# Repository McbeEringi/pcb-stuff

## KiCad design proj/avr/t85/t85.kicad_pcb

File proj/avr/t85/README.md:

# ATtiny85 Micronucleus 開発ボード

## 機能

- 超小型8ピンDIPサイズ
- LEDとボタンを搭載
- EDLC電源基板付き

## 部品

- [ATTiny85](https://akizukidenshi.com/catalog/g/gI-09574/)
- バイパスコンデンサ 1608サイズ 大きめに4.7uFとか
- [表面実装タクトスイッチ](https://akizukidenshi.com/catalog/g/gP-14888/)
- LED
  - 1608サイズ LED
  - 1608サイズ LED電流制限抵抗 10kとか
- USB部
  - CC用抵抗 1608サイズ 5.1k *2
  - ダンピング抵抗 1608サイズ 100R(47Rも可) *2
  - プルアップ抵抗 1608サイズ 1.5k
  - [ツェナーダイオード 3.6v SOD323Fパッケージ(UMD2)](https://akizukidenshi.com/catalog/g/gI-07435/) *2

## 組み立て

表にスイッチとチップ部品

```text
 | USB |
   S W
     101
     -Z<-
-|<- 101
103  -Z<-
-||- 152
```

裏にattiny85と5k1*2
シルクが長いところに凹みを合わせる

SW@PB0
LED@PB1

## ブートローダーの書き込み

<https://github.com/micronucleus/micronucleus>をビルド
windowsはドライバをインストール
ファームウェアをISP書き込み機を用いてを書き込む

参考
<https://qiita.com/nak435/items/67aca33ca49b6f328faa>

## 作例

4和音電子オルゴール <https://github.com/McbeEringi/avr-musicbox>

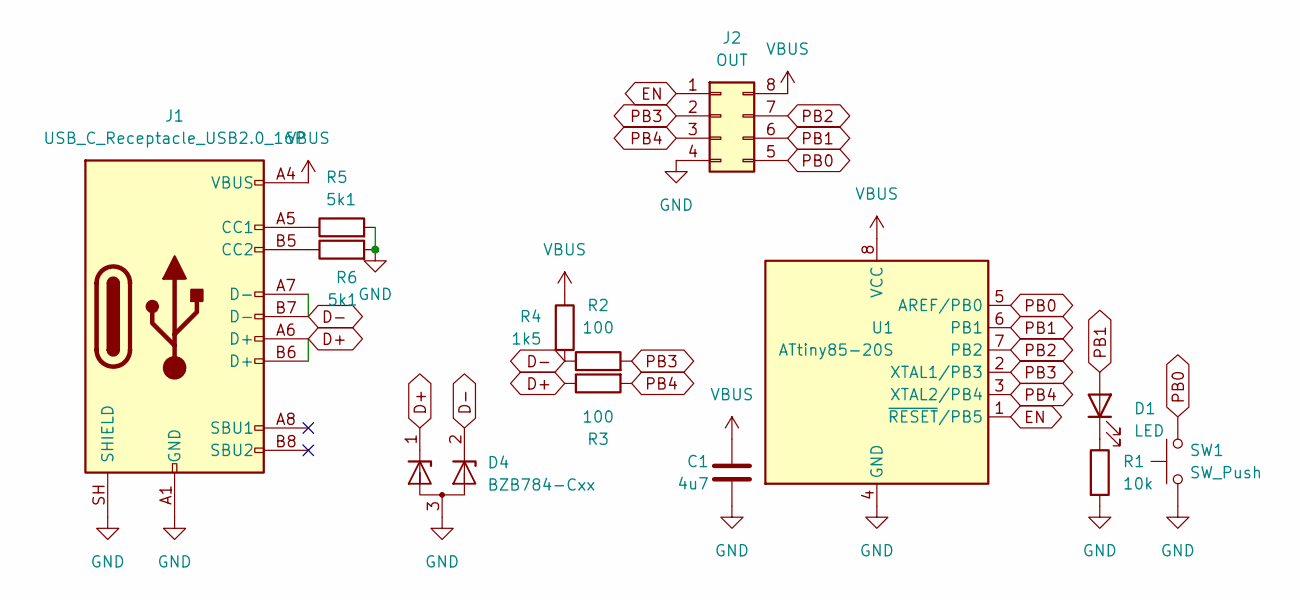
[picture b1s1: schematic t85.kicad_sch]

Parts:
C1: 4u7; C_0603_1608Metric
D1: LED; LED_0603_1608Metric
D4: BZB784-Cxx; SOT-323_SC-70
J1: USB_C_Receptacle_USB2.0_16P; USB_C_Receptacle_GCT_USB4105-xx-A_16P_TopMnt_Horizontal
J2: OUT; DIP-8_W7.62mm_Socket
R1: 10k; R_0603_1608Metric
R2, R3: 100; R_0603_1608Metric
R4: 1k5; R_0603_1608Metric
R5, R6: 5k1; R_0603_1608Metric
SW1: SW_Push; alps-skrp
U1: ATtiny85-20S; SOIC-8_5.3x5.3mm_P1.27mm

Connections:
D+: D4.1 (K), J1.A6 (D+), J1.B6 (D+), R3.1
D-: D4.2 (K), J1.A7 (D-), J1.B7 (D-), R2.1, R4.2
EN: J2.1, U1.1 (~RESET/PB5)
GND: C1.2, D4.3 (A), J1.A1 (GND), J1.A12 (GND), J1.B1 (GND), J1.B12 (GND), J1.SH (SHIELD), J2.4, R1.2, R5.2, R6.2, SW1.1, U1.4 (GND)
unnamed: D1.1 (K), R1.1
unnamed: J1.A5 (CC1), R5.1
unnamed: J1.B5 (CC2), R6.1
PB0: J2.5, SW1.2, U1.5 (AREF/PB0)
PB1: D1.2 (A), J2.6, U1.6 (PB1)
PB2: J2.7, U1.7 (PB2)
PB3: J2.2, R2.2, U1.2 (XTAL1/PB3)
PB4: J2.3, R3.2, U1.3 (XTAL2/PB4)
VBUS: C1.1, J1.A4 (VBUS), J1.A9 (VBUS), J1.B4 (VBUS), J1.B9 (VBUS), J2.8, R4.1, U1.8 (VCC)

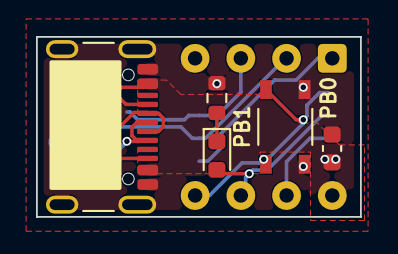
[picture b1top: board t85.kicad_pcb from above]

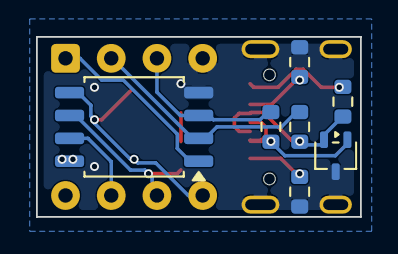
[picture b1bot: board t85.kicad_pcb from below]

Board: 2 copper layers, 18.0 x 10.0 mm, 13 parts (7 on the bottom side), 13 nets.

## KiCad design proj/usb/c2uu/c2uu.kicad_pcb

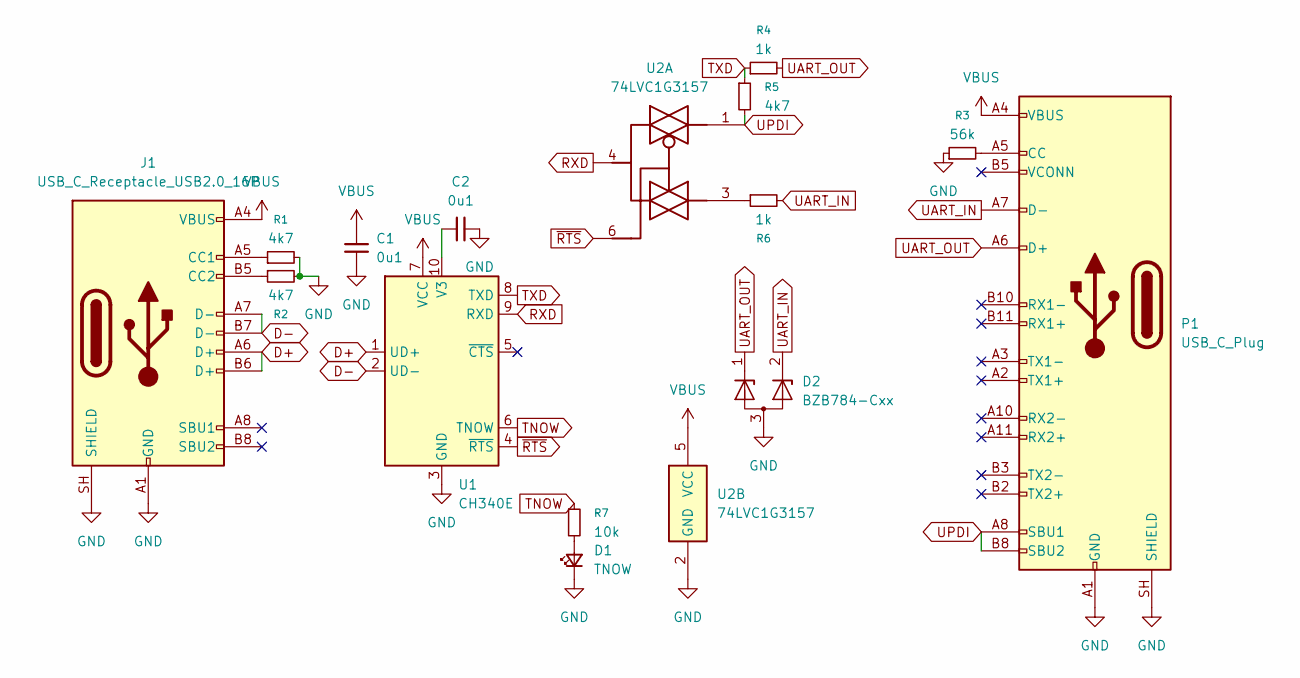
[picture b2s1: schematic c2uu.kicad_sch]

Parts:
C1, C2: 0u1; C_0603_1608Metric
D1: TNOW; LED_0603_1608Metric
D2: BZB784-Cxx; SOT-323_SC-70
J1: USB_C_Receptacle_USB2.0_16P; USB_C_Receptacle_GCT_USB4105-xx-A_16P_TopMnt_Horizontal
P1: USB_C_Plug; USB_C_Plug_24P
R1, R2, R5: 4k7; R_0603_1608Metric
R3: 56k; R_0603_1608Metric
R4, R6: 1k; R_0603_1608Metric
R7: 10k; R_0603_1608Metric
U1: CH340E; MSOP-10_3x3mm_P0.5mm
U2: 74LVC1G3157; SOT-363_SC-70-6

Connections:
D+: J1.A6 (D+), J1.B6 (D+), U1.1 (UD+)
D-: J1.A7 (D-), J1.B7 (D-), U1.2 (UD-)
GND: C1.2, C2.2, D1.1 (K), D2.3 (A), J1.A1 (GND), J1.A12 (GND), J1.B1 (GND), J1.B12 (GND), J1.SH (SHIELD), P1.A1 (GND), P1.A12 (GND), P1.B1 (GND), P1.B12 (GND), P1.SH (SHIELD), R1.2, R2.2, R3.1, U1.3 (GND), U2.2 (GND)
unnamed: D1.2 (A), R7.2
unnamed: J1.A5 (CC1), R1.1
unnamed: J1.B5 (CC2), R2.1
unnamed: P1.A5 (CC), R3.2
unnamed: R6.1, U2.3
unnamed: C2.1, U1.10 (V3)
RXD: U1.9 (RXD), U2.4
TNOW: R7.1, U1.6 (TNOW)
TXD: R4.1, R5.1, U1.8 (TXD)
UART_IN: D2.2 (K), P1.A7 (D-), R6.2
UART_OUT: D2.1 (K), P1.A6 (D+), R4.2
UPDI: P1.A8 (SBU1), P1.B8 (SBU2), R5.2, U2.1
VBUS: C1.1, J1.A4 (VBUS), J1.A9 (VBUS), J1.B4 (VBUS), J1.B9 (VBUS), P1.A4 (VBUS), P1.A9 (VBUS), P1.B4 (VBUS), P1.B9 (VBUS), U1.7 (VCC), U2.5 (VCC)
~RTS: U1.4 (~RTS), U2.6

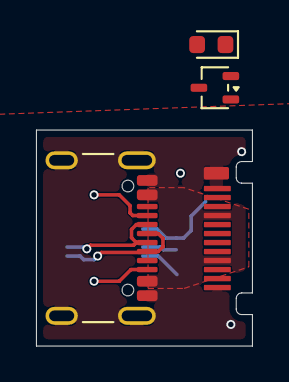
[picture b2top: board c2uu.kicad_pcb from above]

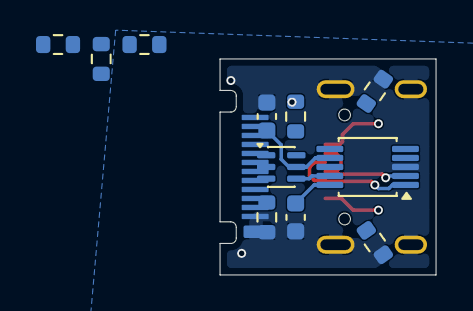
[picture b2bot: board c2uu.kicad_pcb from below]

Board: 2 copper layers, 12.0 x 12.0 mm, 15 parts (12 on the bottom side), 17 nets.

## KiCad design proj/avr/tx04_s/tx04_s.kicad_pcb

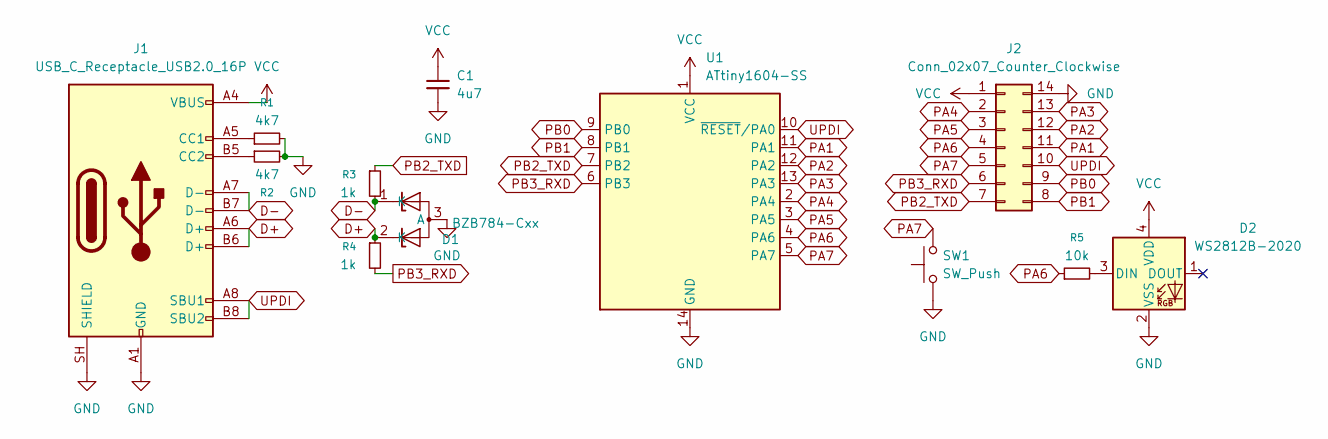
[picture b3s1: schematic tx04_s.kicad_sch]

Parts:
C1: 4u7; C_0603_1608Metric
D1: BZB784-Cxx; SOT-323_SC-70
D2: WS2812B-2020; LED_WS2812B-2020_PLCC4_2.0x2.0mm
J1: USB_C_Receptacle_USB2.0_16P; USB_C_Receptacle_GCT_USB4105-xx-A_16P_TopMnt_Horizontal
J2: Conn_02x07_Counter_Clockwise; DIP-14_W10.16mm
R1, R2: 4k7; R_0603_1608Metric
R3, R4: 1k; R_0603_1608Metric
R5: 10k; R_0603_1608Metric
SW1: SW_Push; alps-skrp
U1: ATtiny1604-SS; SOIC-14_3.9x8.7mm_P1.27mm

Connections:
D+: D1.2 (K), J1.A6 (D+), J1.B6 (D+), R4.1
D-: D1.1 (K), J1.A7 (D-), J1.B7 (D-), R3.2
GND: C1.2, D1.3 (A), D2.2 (VSS), J1.A1 (GND), J1.A12 (GND), J1.B1 (GND), J1.B12 (GND), J1.SH (SHIELD), J2.14, R1.2, R2.2, SW1.1, U1.14 (GND)
unnamed: D2.3 (DIN), R5.2
unnamed: J1.A5 (CC1), R1.1
unnamed: J1.B5 (CC2), R2.1
PA1: J2.11, U1.11 (PA1)
PA2: J2.12, U1.12 (PA2)
PA3: J2.13, U1.13 (PA3)
PA4: J2.2, U1.2 (PA4)
PA5: J2.3, U1.3 (PA5)
PA6: J2.4, R5.1, U1.4 (PA6)
PA7: J2.5, SW1.2, U1.5 (PA7)
PB0: J2.9, U1.9 (PB0)
PB1: J2.8, U1.8 (PB1)
PB2_TXD: J2.7, R3.1, U1.7 (PB2)
PB3_RXD: J2.6, R4.2, U1.6 (PB3)
UPDI: J1.A8 (SBU1), J1.B8 (SBU2), J2.10, U1.10 (~RESET/PA0)
VCC: C1.1, D2.4 (VDD), J1.A4 (VBUS), J1.A9 (VBUS), J1.B4 (VBUS), J1.B9 (VBUS), J2.1, U1.1 (VCC)

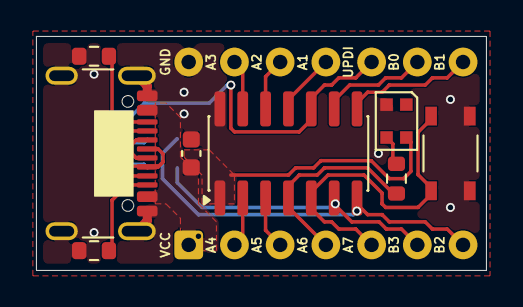
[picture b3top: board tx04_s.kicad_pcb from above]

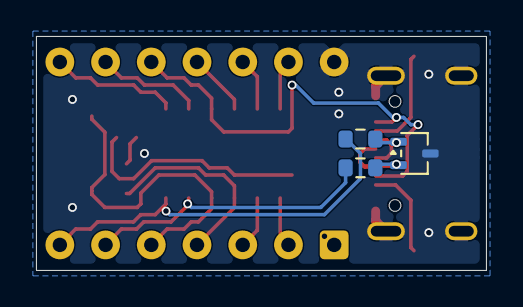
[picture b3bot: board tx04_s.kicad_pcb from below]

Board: 2 copper layers, 25.0 x 13.0 mm, 12 parts (3 on the bottom side), 19 nets.

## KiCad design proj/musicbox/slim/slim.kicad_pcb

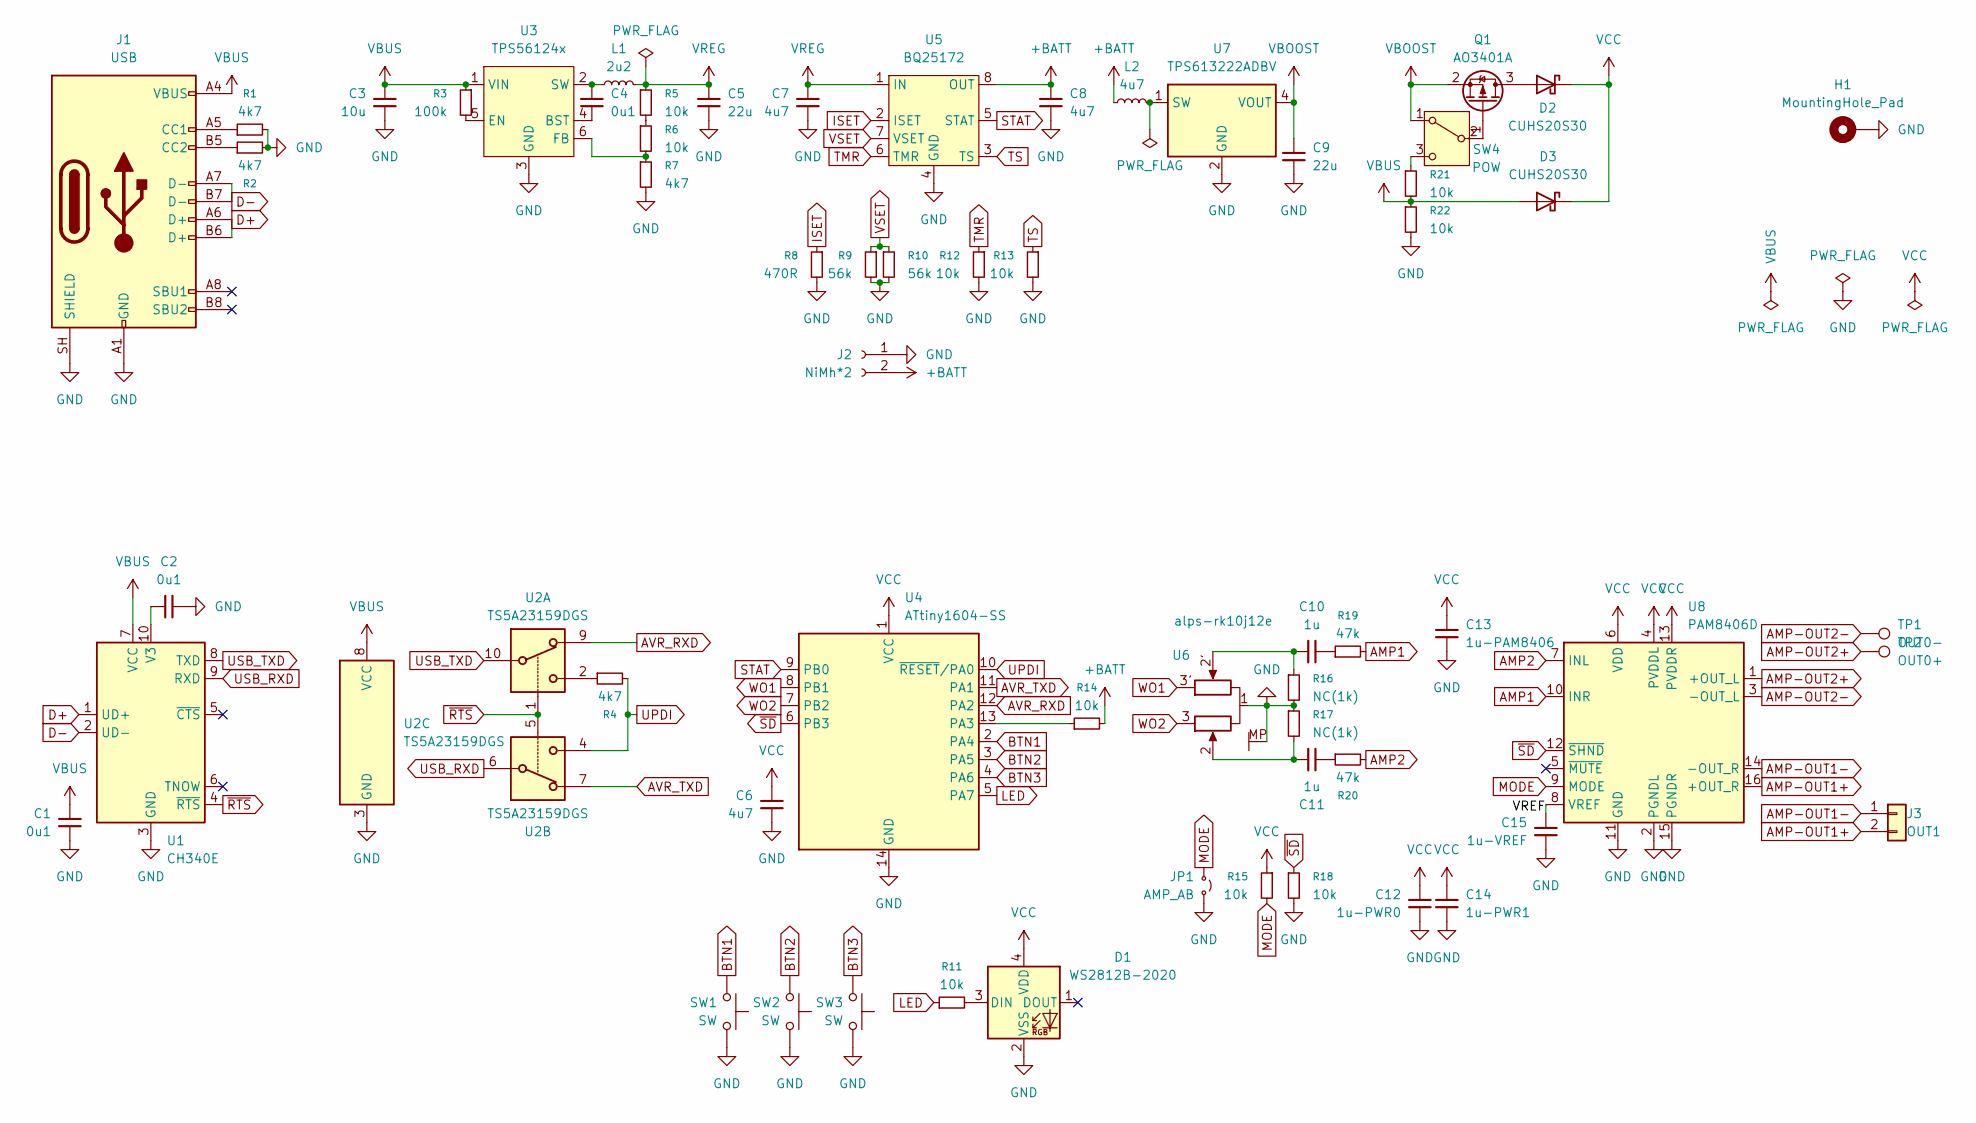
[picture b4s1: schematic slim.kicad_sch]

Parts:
C1, C2, C4: 0u1; C_0603_1608Metric
C3: 10u; C_0603_1608Metric
C5, C9: 22u; C_0603_1608Metric
C6, C7, C8: 4u7; C_0603_1608Metric
C10, C11: 1u; C_0603_1608Metric
C12: 1u-PWR0; C_0603_1608Metric
C13: 1u-PAM8406; C_0603_1608Metric
C14: 1u-PWR1; C_0603_1608Metric
C15: 1u-VREF; C_0603_1608Metric
D1: WS2812B-2020; LED_WS2812B-2020_PLCC4_2.0x2.0mm
D2, D3: CUHS20S30; US2H
H1: MountingHole_Pad; MountingHole_3.2mm_M3_Pad
J1: USB; USB_C_Receptacle_GCT_USB4105-xx-A_16P_TopMnt_Horizontal
J2: NiMh*2; JST_XH_B2B-XH-A_1x02_P2.50mm_Vertical
J3: OUT1; JST_ZH_B2B-ZR_1x02_P1.50mm_Vertical
JP1: AMP_AB; R_0603_1608Metric
L1: 2u2; L_0805_2012Metric
L2: 4u7; L_1008_2520Metric
Q1: AO3401A; SOT-23
R1, R2, R4, R7: 4k7; R_0603_1608Metric
R3: 100k; R_0603_1608Metric
R5, R6, R11, R12, R13, R14, R15, R18, R21, R22: 10k; R_0603_1608Metric
R8: 470R; R_0603_1608Metric
R9, R10: 56k; R_0603_1608Metric
R16, R17: NC(1k); R_0603_1608Metric
R19, R20: 47k; R_0603_1608Metric
SW1, SW2, SW3: SW; alps-skr[gp]
SW4: POW; IS-1245T-G
TP1: OUT0-; TestPoint_Pad_1.5x1.5mm
TP2: OUT0+; TestPoint_Pad_D1.5mm
U1: CH340E; MSOP-10_3x3mm_P0.5mm
U2: TS5A23159DGS; TSSOP-10_3x3mm_P0.5mm
U3: TPS56124x; SOT-563
U4: ATtiny1604-SS; SOIC-14_3.9x8.7mm_P1.27mm
U5: BQ25172; Texas_DSG0008A_WSON-8-1EP_2x2mm_P0.5mm_EP0.9x1.6mm
U6: alps-rk10j12e
U7: TPS613222ADBV; SOT-23-5
U8: PAM8406D; SOIC-16_3.9x9.9mm_P1.27mm

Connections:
+BATT: C8.2, J2.2, L2.1, R14.2, U5.8 (OUT)
/VREF: C15.2, U8.8 (VREF)
AMP1: R19.2, U8.10 (INR)
AMP2: R20.2, U8.7 (INL)
AMP-OUT1+: J3.2, U8.16 (+OUT_R)
AMP-OUT1-: J3.1, U8.14 (-OUT_R)
AMP-OUT2+: TP2.1 (1_1), U8.1 (+OUT_L)
AMP-OUT2-: TP1.1 (1_1), U8.3 (-OUT_L)
AVR_RXD: U2.9, U4.12 (PA2)
AVR_TXD: U2.7, U4.11 (PA1)
BTN1: SW1.2, U4.2 (PA4)
BTN2: SW2.2, U4.3 (PA5)
BTN3: SW3.2, U4.4 (PA6)
D+: J1.A6 (D+), J1.B6 (D+), U1.1 (UD+)
D-: J1.A7 (D-), J1.B7 (D-), U1.2 (UD-)
GND: C1.1, C2.2, C3.1, C5.2, C6.1, C7.1, C8.1, C9.2, C12.1, C13.1, C14.1, C15.1, D1.2 (VSS), H1.1 (1_1), J1.A1 (GND), J1.A12 (GND), J1.B1 (GND), J1.B12 (GND), J1.SH (SHIELD), J2.1, JP1.1 (A), R1.2, R2.2, R7.2, R8.2, R9.2, R10.2, R12.2, R13.2, R16.2, R17.1, R18.2, R22.2, SW1.1, SW2.1, SW3.1, U1.3 (GND), U2.3 (GND), U3.3 (GND), U4.14 (GND), U5.4 (GND), U5.9 (GND), U6.1, U6.MP, U7.2 (GND), U8.2 (PGNDL), U8.11 (GND), U8.15 (PGNDR)
ISET: R8.1, U5.2 (ISET)
LED: R11.1, U4.5 (PA7)
MODE: JP1.2 (B), R15.2, U8.9 (MODE)
unnamed: C10.1, R16.1, U6.2'
unnamed: C10.2, R19.1
unnamed: C11.1, R17.2, U6.2
unnamed: C11.2, R20.1
unnamed: D1.3 (DIN), R11.2
unnamed: D2.2 (A), Q1.3 (D)
unnamed: J1.A5 (CC1), R1.1
unnamed: J1.B5 (CC2), R2.1
unnamed: Q1.1 (G), SW4.2 (B)
unnamed: R4.1, U2.2
unnamed: R5.2, R6.1
unnamed: R21.1, SW4.3 (C)
unnamed: C2.1, U1.10 (V3)
unnamed: C4.1, U3.4 (BST)
unnamed: R3.2, U3.5 (EN)
unnamed: R6.2, R7.1, U3.6 (FB)
unnamed: C4.2, L1.1, U3.2 (SW)
unnamed: R14.1, U4.13 (PA3)
unnamed: L2.2, U7.1 (SW)
STAT: U4.9 (PB0), U5.5 (STAT)
TMR: R12.1, U5.6 (TMR)
TS: R13.1, U5.3 (TS)
UPDI: R4.2, U2.4, U4.10 (~RESET/PA0)
USB_RXD: U1.9 (RXD), U2.6
USB_TXD: U1.8 (TXD), U2.10
VBOOST: C9.1, Q1.2 (S), SW4.1 (A), U7.4 (VOUT)
VBUS: C1.2, C3.2, D3.2 (A), J1.A4 (VBUS), J1.A9 (VBUS), J1.B4 (VBUS), J1.B9 (VBUS), R3.1, R21.2, R22.1, U1.7 (VCC), U2.8 (VCC), U3.1 (VIN)
VCC: C6.2, C12.2, C13.2, C14.2, D1.4 (VDD), D2.1 (K), D3.1 (K), R15.1, U4.1 (VCC), U8.4 (PVDDL), U8.6 (VDD), U8.13 (PVDDR)
VREG: C5.1, C7.2, L1.2, R5.1, U5.1 (IN)
VSET: R9.1, R10.1, U5.7 (VSET)
WO1: U4.8 (PB1), U6.3'
WO2: U4.7 (PB2), U6.3
~RTS: U1.4 (~RTS), U2.1, U2.5
~SD: R18.1, U4.6 (PB3), U8.12 (~SHND)

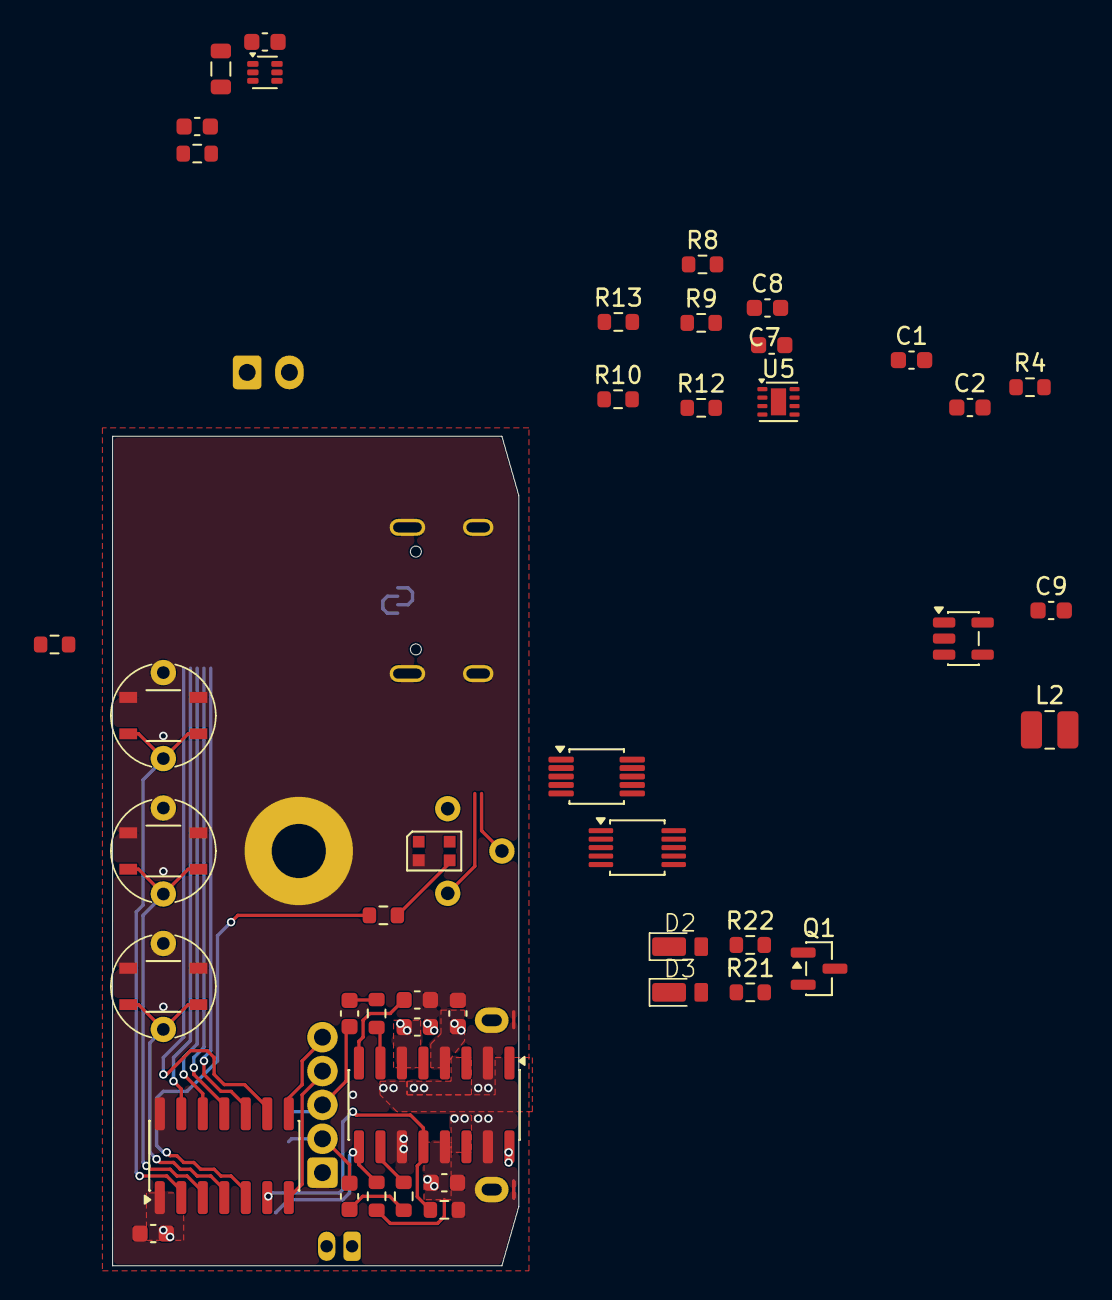
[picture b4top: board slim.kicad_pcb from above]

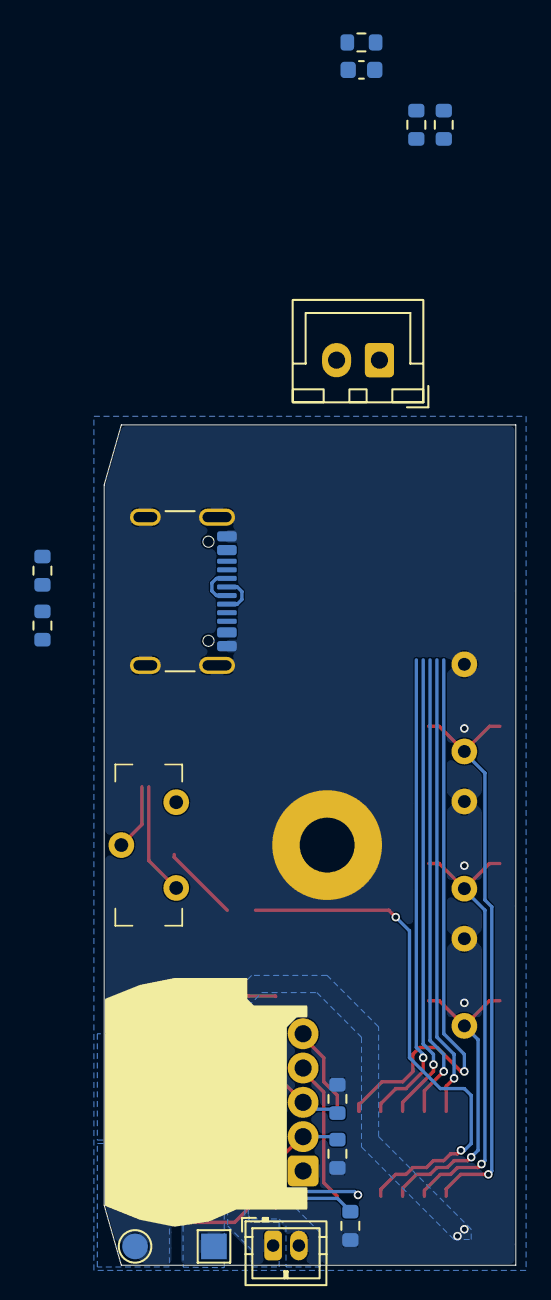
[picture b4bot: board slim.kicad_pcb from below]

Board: 2 copper layers, 24.0 x 49.0 mm, 62 parts (17 on the bottom side), 53 nets.

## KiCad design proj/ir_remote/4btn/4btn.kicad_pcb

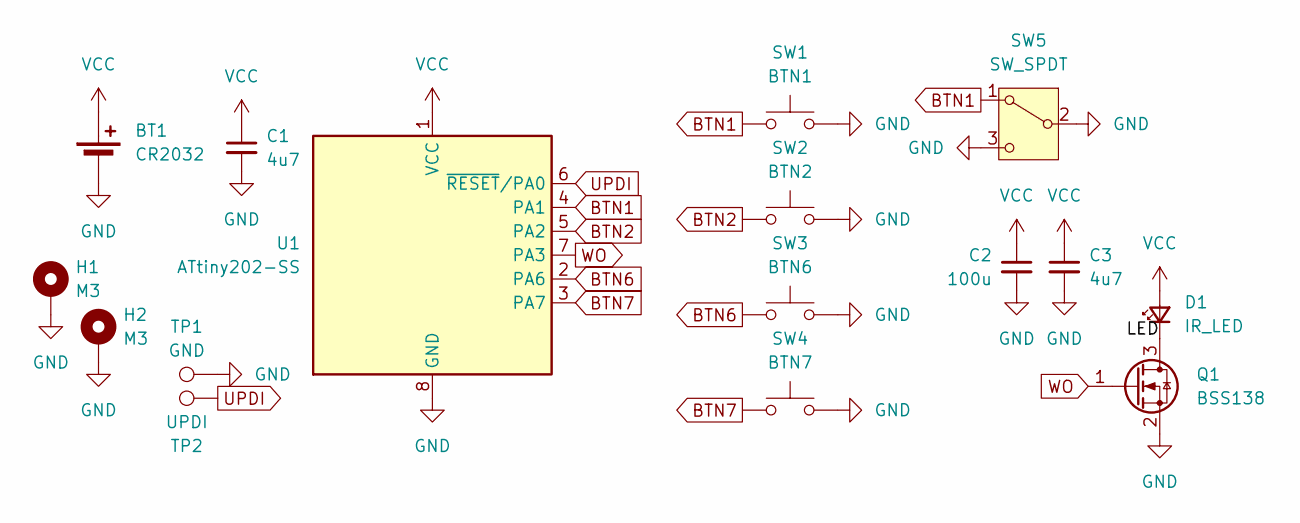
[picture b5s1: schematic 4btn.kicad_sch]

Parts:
BT1: CR2032; BatteryHolder_Multicomp_BC-2001_1x2032
C1, C3: 4u7; C_0603_1608Metric
C2: 100u; C_1206_3216Metric
D1: IR_LED; LED_D5.0mm_Horizontal_O1.27mm_Z3.0mm_Clear
H1, H2: M3; MountingHole_3.2mm_M3_Pad
Q1: BSS138; SOT-23
SW1: BTN1; alps-skrg
SW2: BTN2; alps-skrg
SW3: BTN6; alps-skrg
SW4: BTN7; alps-skrg
SW5: SW_SPDT; IS-1245T-G
TP1: GND; TestPoint_Pad_1.5x1.5mm
TP2: UPDI; TestPoint_Pad_D1.5mm
U1: ATtiny202-SS; SOIC-8_3.9x4.9mm_P1.27mm

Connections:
/LED: D1.1 (K), Q1.3 (D)
BTN1: SW1.1, SW5.1 (A), U1.4 (PA1)
BTN2: SW2.1, U1.5 (PA2)
BTN6: SW3.1, U1.2 (PA6)
BTN7: SW4.1, U1.3 (PA7)
GND: BT1.2 (-), C1.2, C2.2, C3.2, H1.1 (1_1), H2.1 (1_1), Q1.2 (S), SW1.2, SW2.2, SW3.2, SW4.2, SW5.2 (B), SW5.3 (C), TP1.1 (1_1), U1.8 (GND)
UPDI: TP2.1 (1_1), U1.6 (~RESET/PA0)
VCC: BT1.1 (+), C1.1, C2.1, C3.1, D1.2 (A), U1.1 (VCC)
WO: Q1.1 (G), U1.7 (PA3)

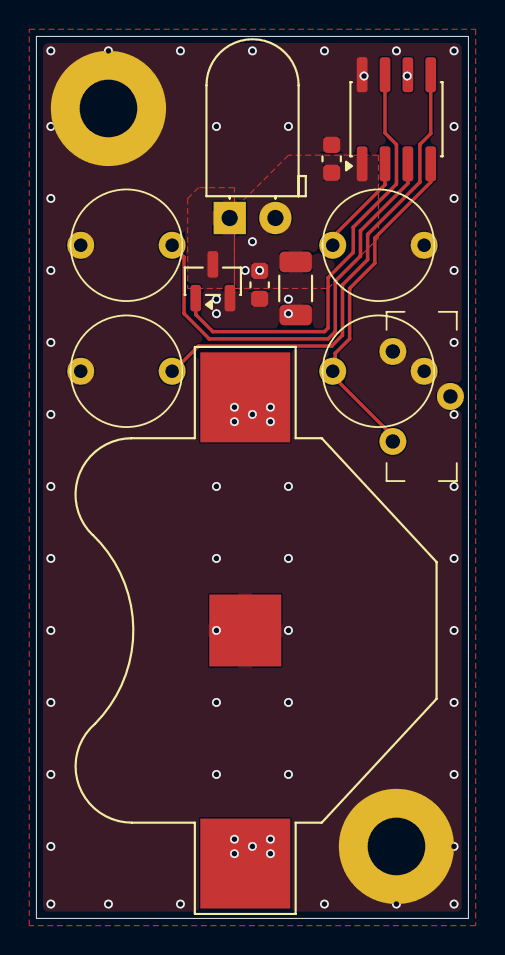
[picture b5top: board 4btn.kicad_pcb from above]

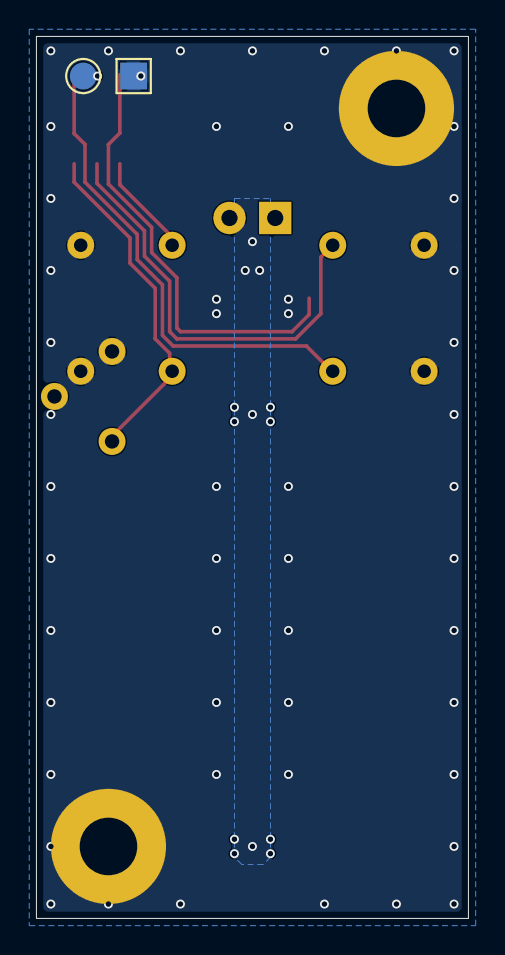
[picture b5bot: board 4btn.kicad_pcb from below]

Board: 2 copper layers, 24.0 x 49.0 mm, 16 parts (2 on the bottom side), 9 nets.

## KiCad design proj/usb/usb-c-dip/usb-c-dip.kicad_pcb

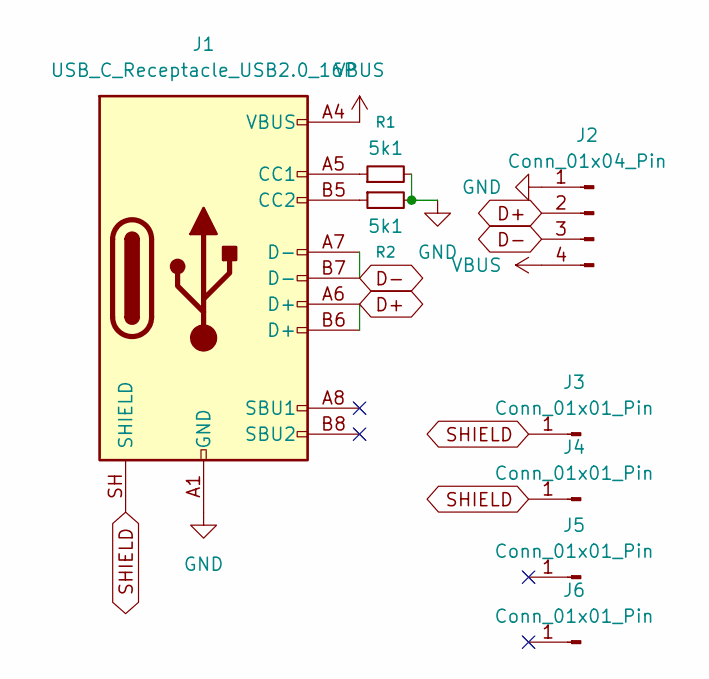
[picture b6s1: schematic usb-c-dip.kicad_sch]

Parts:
J1: USB_C_Receptacle_USB2.0_16P; USB_C_Receptacle_GCT_USB4105-xx-A_16P_TopMnt_Horizontal
J2: Conn_01x04_Pin; PinHeader_1x04_P2.54mm_Vertical
J3, J4, J5, J6: Conn_01x01_Pin; PinHeader_1x01_P2.54mm_Vertical
R1, R2: 5k1; R_0603_1608Metric

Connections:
D+: J1.A6 (D+), J1.B6 (D+), J2.2
D-: J1.A7 (D-), J1.B7 (D-), J2.3
GND: J1.A1 (GND), J1.A12 (GND), J1.B1 (GND), J1.B12 (GND), J2.1, R1.2, R2.2
unnamed: J1.A5 (CC1), R1.1
unnamed: J1.B5 (CC2), R2.1
SHIELD: J1.SH (SHIELD), J3.1 (Pin_1_1), J4.1 (Pin_1_1)
VBUS: J1.A4 (VBUS), J1.A9 (VBUS), J1.B4 (VBUS), J1.B9 (VBUS), J2.4

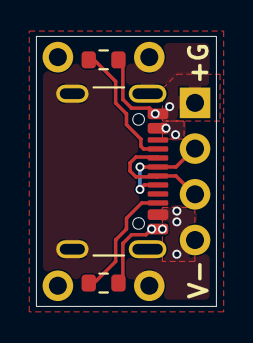
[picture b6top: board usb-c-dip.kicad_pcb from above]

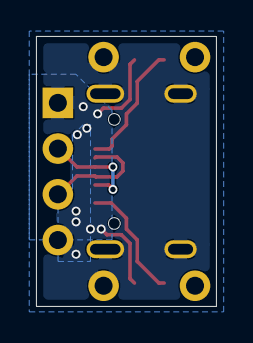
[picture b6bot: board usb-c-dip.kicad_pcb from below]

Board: 2 copper layers, 10.0 x 15.0 mm, 8 parts (5 on the bottom side), 7 nets.

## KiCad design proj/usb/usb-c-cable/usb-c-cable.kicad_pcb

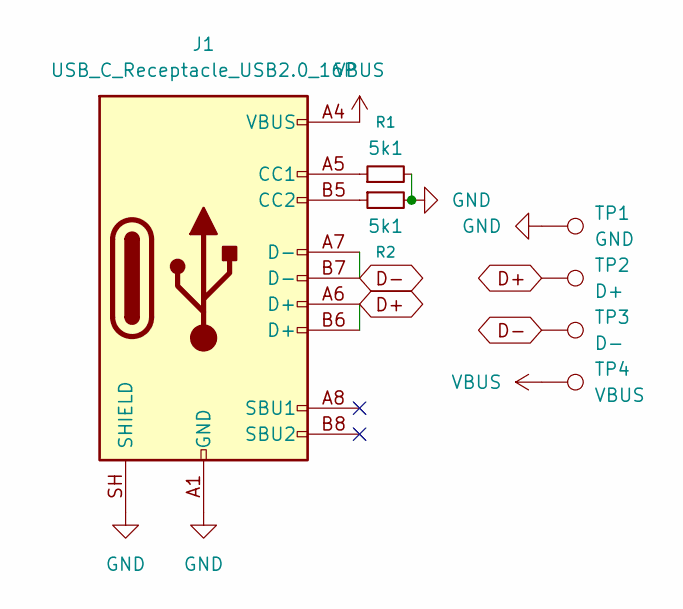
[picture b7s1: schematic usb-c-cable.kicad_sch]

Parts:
J1: USB_C_Receptacle_USB2.0_16P; USB_C_Receptacle_GCT_USB4105-xx-A_16P_TopMnt_Horizontal
R1, R2: 5k1; R_0603_1608Metric
TP1: GND; TestPoint_Pad_1.0x1.0mm
TP2: D+; TestPoint_Pad_D1.0mm
TP3: D-; TestPoint_Pad_D1.0mm
TP4: VBUS; TestPoint_Pad_D1.0mm

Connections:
D+: J1.A6 (D+), J1.B6 (D+), TP2.1 (1_1)
D-: J1.A7 (D-), J1.B7 (D-), TP3.1 (1_1)
GND: J1.A1 (GND), J1.A12 (GND), J1.B1 (GND), J1.B12 (GND), J1.SH (SHIELD), R1.2, R2.2, TP1.1 (1_1)
unnamed: J1.A5 (CC1), R1.1
unnamed: J1.B5 (CC2), R2.1
VBUS: J1.A4 (VBUS), J1.A9 (VBUS), J1.B4 (VBUS), J1.B9 (VBUS), TP4.1 (1_1)

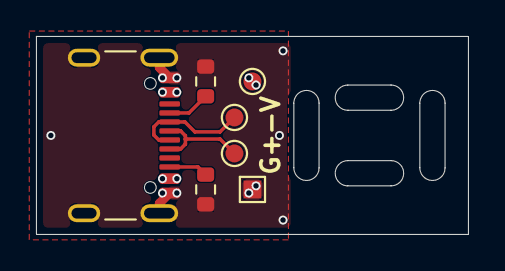
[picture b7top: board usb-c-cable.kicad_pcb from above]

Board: 2 copper layers, 24.0 x 11.0 mm, 7 parts (0 on the bottom side), 6 nets.
